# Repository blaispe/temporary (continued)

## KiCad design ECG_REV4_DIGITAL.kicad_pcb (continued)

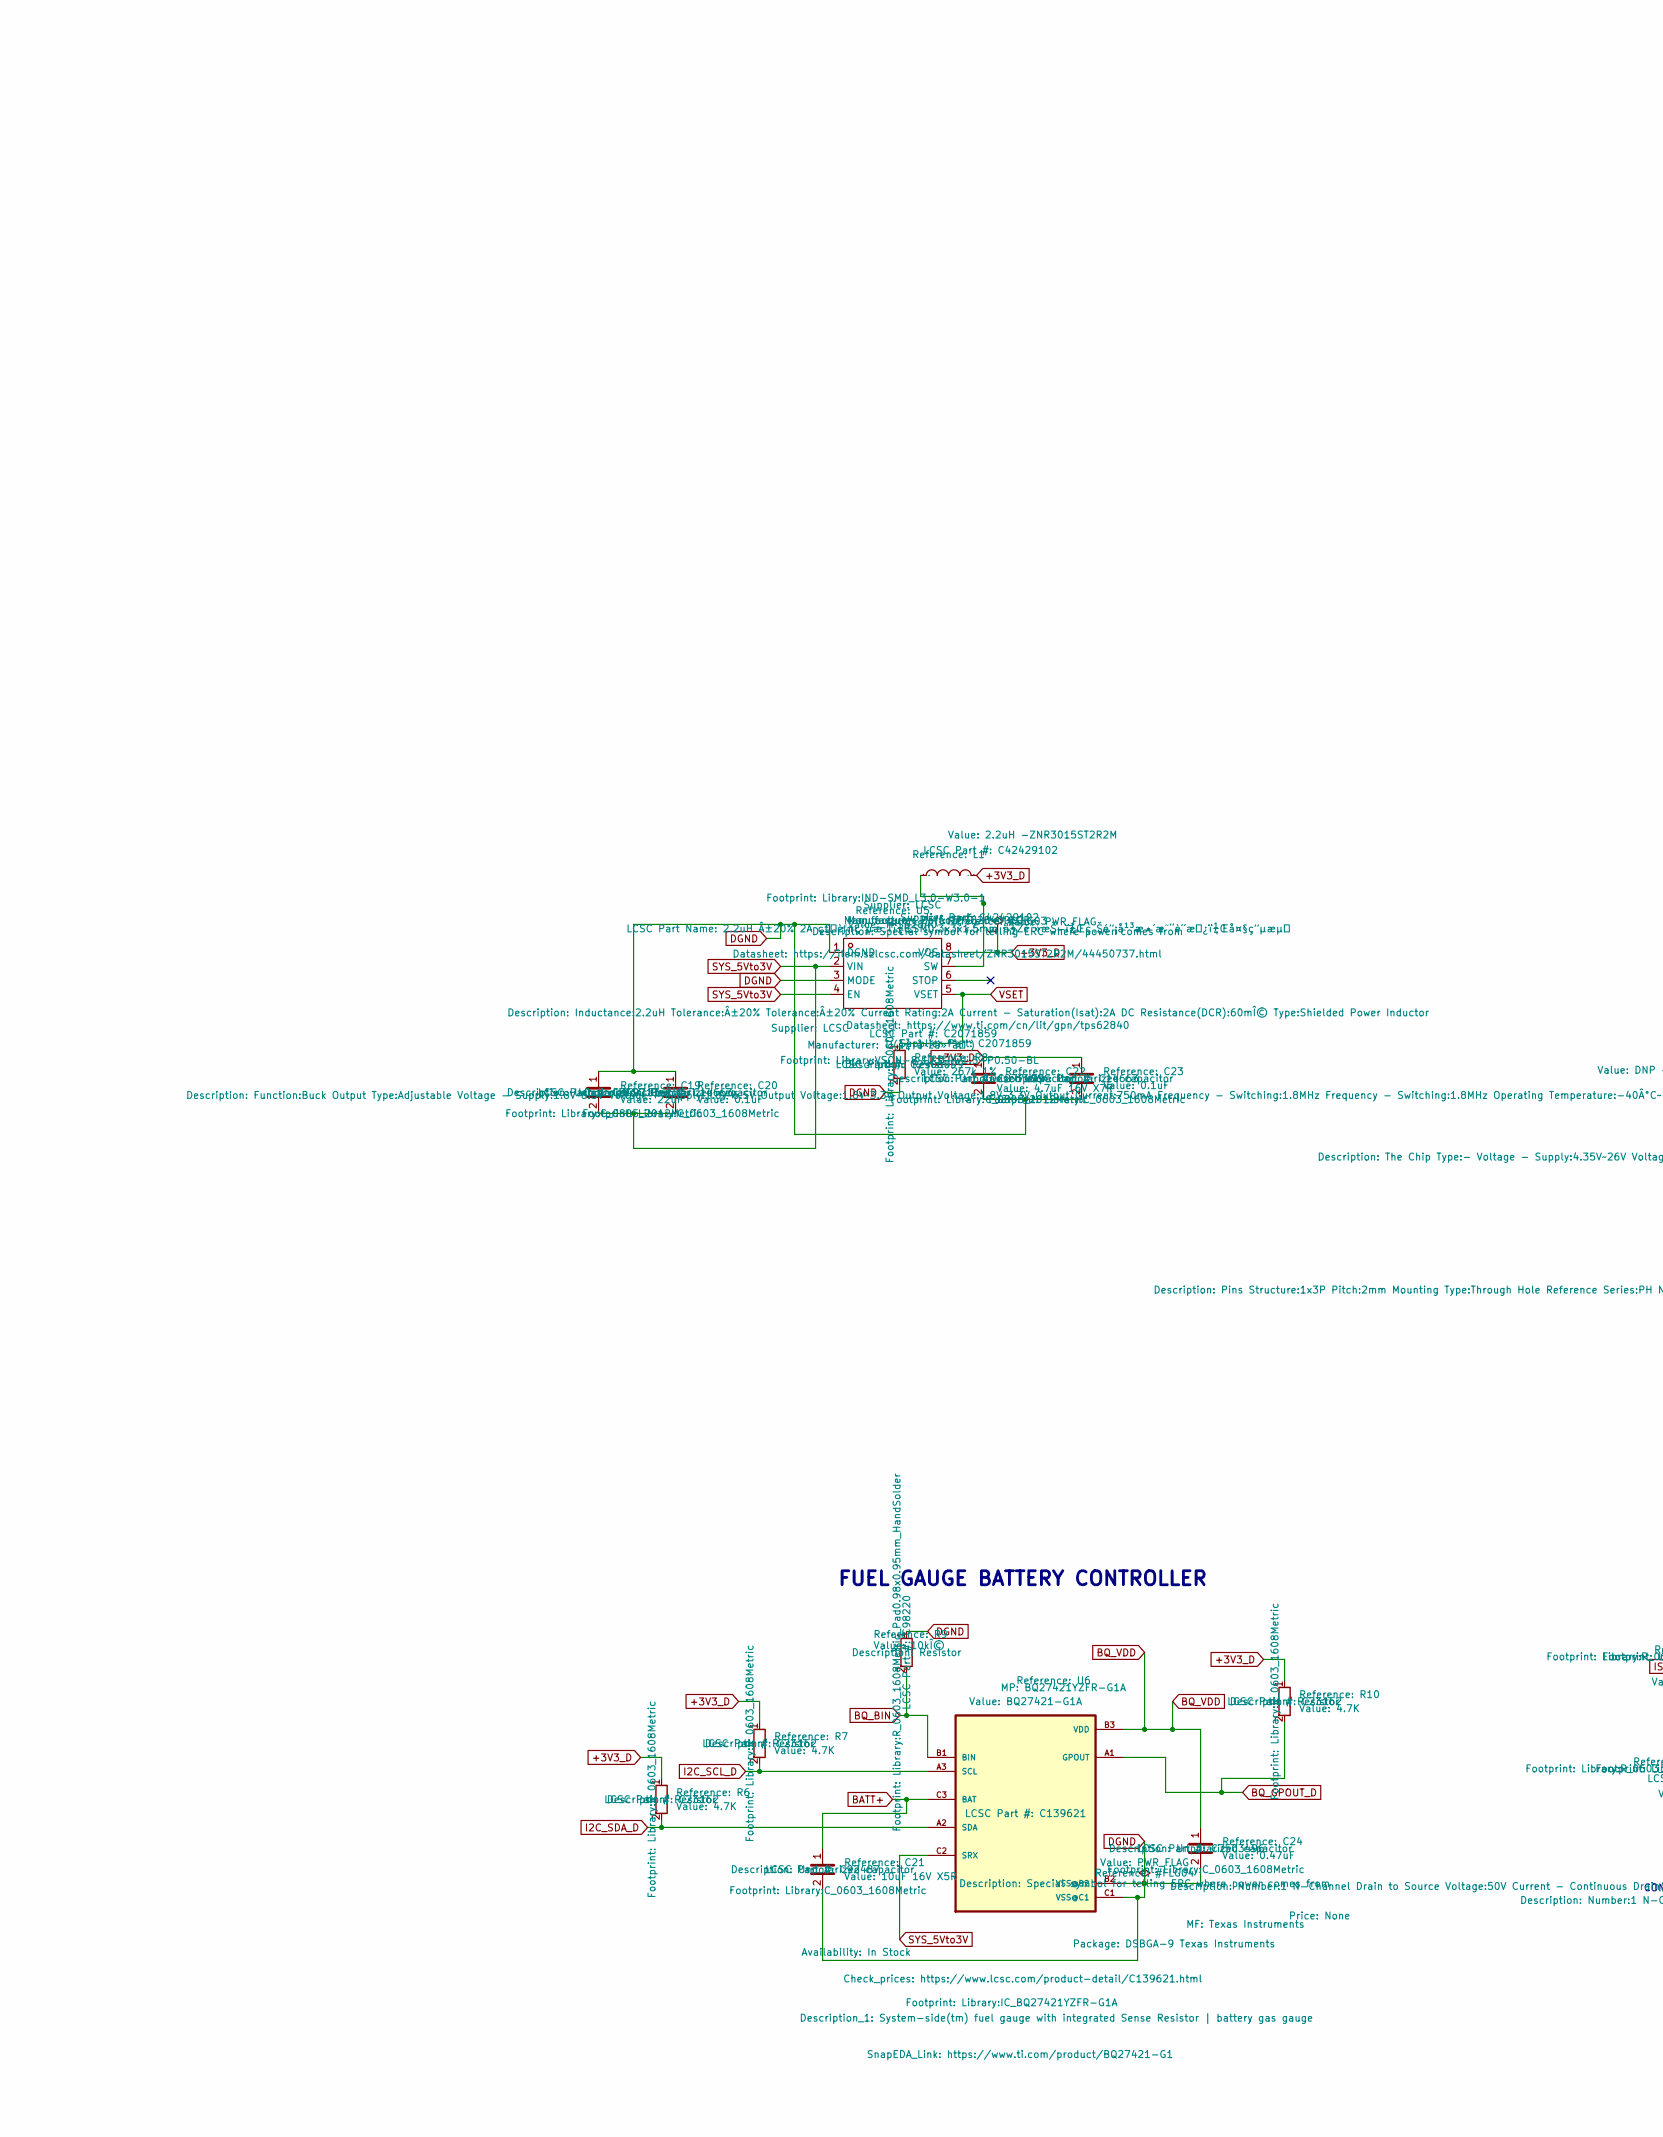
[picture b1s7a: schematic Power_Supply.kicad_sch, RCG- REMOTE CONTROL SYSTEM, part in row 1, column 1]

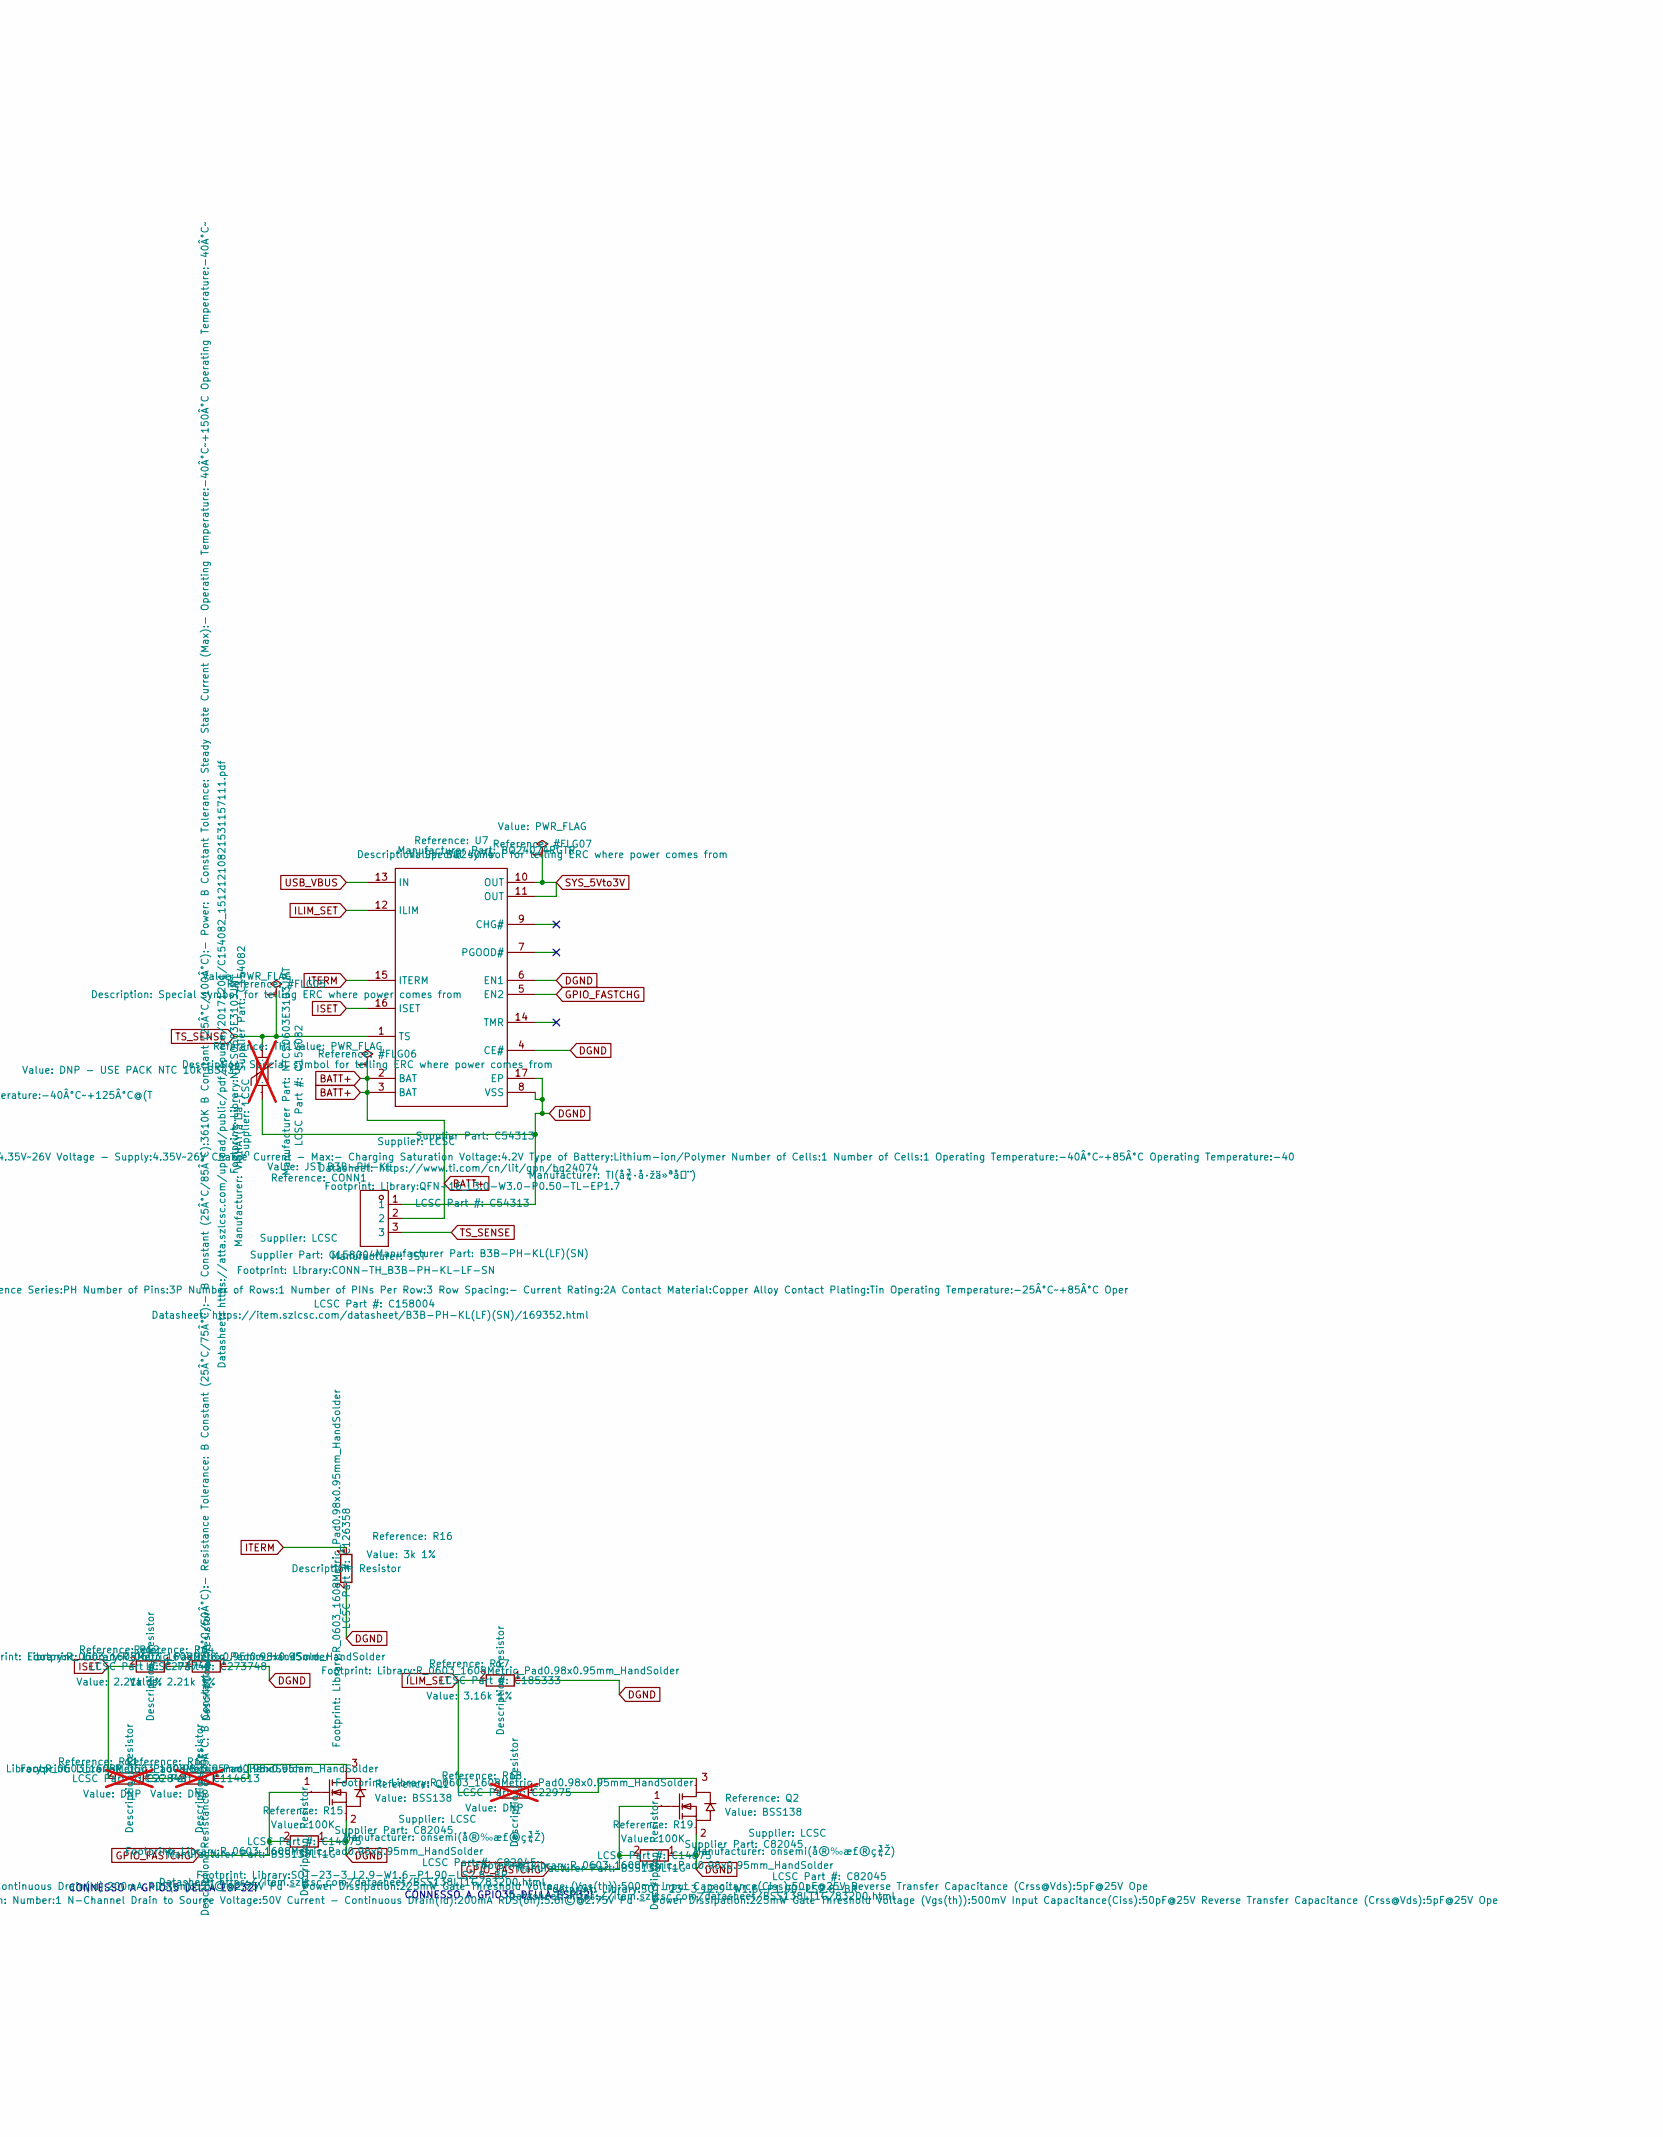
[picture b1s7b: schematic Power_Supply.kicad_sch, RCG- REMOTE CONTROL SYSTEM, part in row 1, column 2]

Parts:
C19: 22uF; C_0805_2012Metric; LCSC Part # C342717
C20, C23: 0.1uF; C_0603_1608Metric; LCSC Part # C14663
C21: 10uF 16V X5R; C_0603_1608Metric; LCSC Part # C92487
C22: 4.7uF 16V X7R; C_0805_2012Metric; LCSC Part # C277499
C24: 0.47uF; C_0603_1608Metric; LCSC Part # C7503496
CONN1: JST B3B-PH-KL; CONN-TH_B3B-PH-KL-LF-SN; Manufacturer Part B3B-PH-KL(LF)(SN); LCSC Part # C158004
L1: 2.2uH -ZNR3015ST2R2M; IND-SMD_L3.0-W3.0-1; LCSC Part # C42429102
Q1, Q2: BSS138; SOT-23-3_L2.9-W1.6-P1.90-LS2.8-BR; Manufacturer Part BSS138LT1G; LCSC Part # C82045
R6, R7, R10: 4.7K; R_0603_1608Metric; LCSC Part # C23162
R8: 267k 1%; R_0603_1608Metric; LCSC Part # C2906999
R9: 10kÎ©; R_0603_1608Metric_Pad0.98x0.95mm_HandSolder; LCSC Part # C98220
R11: DNP; R_0603_1608Metric_Pad0.98x0.95mm_HandSolder; LCSC Part # C22843; not fitted
R12, R14: 2.21k 1%; R_0603_1608Metric_Pad0.98x0.95mm_HandSolder; LCSC Part # C273748
R13: DNP; R_0603_1608Metric_Pad0.98x0.95mm_HandSolder; LCSC Part # C114613; not fitted
R15, R19: 100K; R_0603_1608Metric_Pad0.98x0.95mm_HandSolder; LCSC Part # C14675
R16: 3k 1%; R_0603_1608Metric_Pad0.98x0.95mm_HandSolder; LCSC Part # C126358
R17: 3.16k 1%; R_0603_1608Metric_Pad0.98x0.95mm_HandSolder; LCSC Part # C185333
R18: DNP; R_0603_1608Metric_Pad0.98x0.95mm_HandSolder; LCSC Part # C22975; not fitted
TH1: DNP - USE PACK NTC 10k B3435; NTCS0603E3103JMT; Manufacturer Part NTCS0603E3103JMT; LCSC Part # C154082; not fitted
U5: TPS62840; VSON-8_L2.0-W1.5-P0.50-BL; Manufacturer Part TPS62840DLCR; LCSC Part # C2071859
U6: BQ27421-G1A; IC_BQ27421YZFR-G1A; LCSC Part # C139621
U7: BQ24074; QFN-16_L3.0-W3.0-P0.50-TL-EP1.7; Manufacturer Part BQ24074RGTR; LCSC Part # C54313

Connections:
+3V3_D: C22.1, C23.1, L1.2, R6.1, R7.1, R10.1, U5.8 (VOS); also elsewhere on the board
BATT+: C21.1, CONN1.2, U6.C3 (BAT), U7.2 (BAT), U7.3 (BAT)
BQ_BIN: R9.2, U6.B1 (BIN)
BQ_GPOUT_D: R10.2, U6.A1 (GPOUT); also elsewhere on the board
BQ_VDD: C24.1, U6.B3 (VDD)
DGND: C19.1, C20.1, C21.2, C22.2, C23.2, C24.2, CONN1.1, Q1.2 (S), Q2.2 (S), R8.2, R9.1, R14.1, R15.1, R16.2, R17.1, R19.1, TH1.1, U5.1 (DGND), U5.3 (MODE), U6.B2 (VSS@B2), U6.C1 (VSS@C1), U7.4 (CE#), U7.6 (EN1), U7.8 (VSS), U7.17 (EP); also elsewhere on the board
GPIO_FASTCHG: Q1.1 (G), Q2.1 (G), R15.2, R19.2, U7.5 (EN2); also elsewhere on the board
I2C_SCL_D: R7.2, U6.A3 (SCL); also elsewhere on the board
I2C_SDA_D: R6.2, U6.A2 (SDA); also elsewhere on the board
ILIM_SET: R17.2, R18.2, U7.12 (ILIM)
ISET: R11.2, R12.2, U7.16 (ISET)
ITERM: R16.1, U7.15 (ITERM)
unnamed: Q1.3 (D), R13.1
unnamed: Q2.3 (D), R18.1
unnamed: R11.1, R13.2
unnamed: R12.1, R14.2
unnamed: L1.1, U5.7 (SW)
SYS_5Vto3V: C19.2, C20.2, U5.2 (VIN), U5.4 (EN), U6.C2 (SRX), U7.10 (OUT), U7.11 (OUT)
TS_SENSE: CONN1.3, TH1.2, U7.1 (TS)
USB_VBUS: U7.13 (IN); also elsewhere on the board
VSET: R8.1, U5.5 (VSET)

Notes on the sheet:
FUEL GAUGE BATTERY CONTROLLER
CONNESSO A GPIO35 DELLA ESP32!

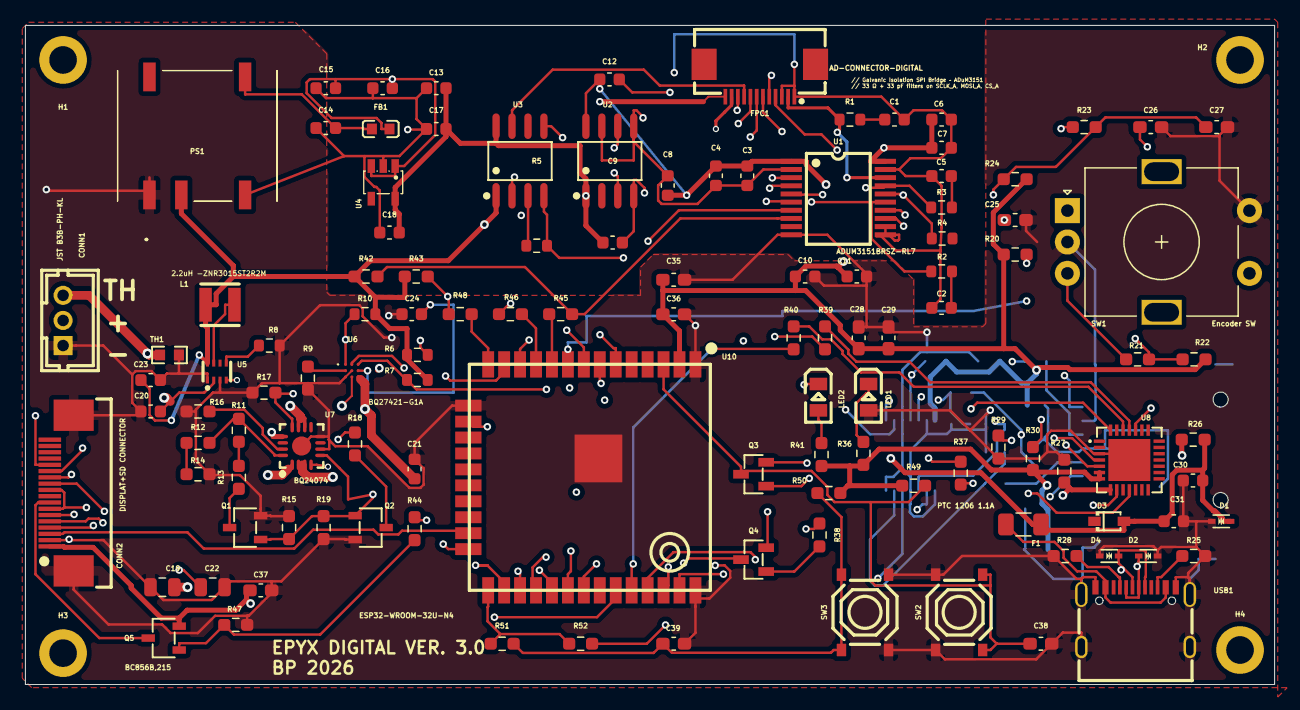
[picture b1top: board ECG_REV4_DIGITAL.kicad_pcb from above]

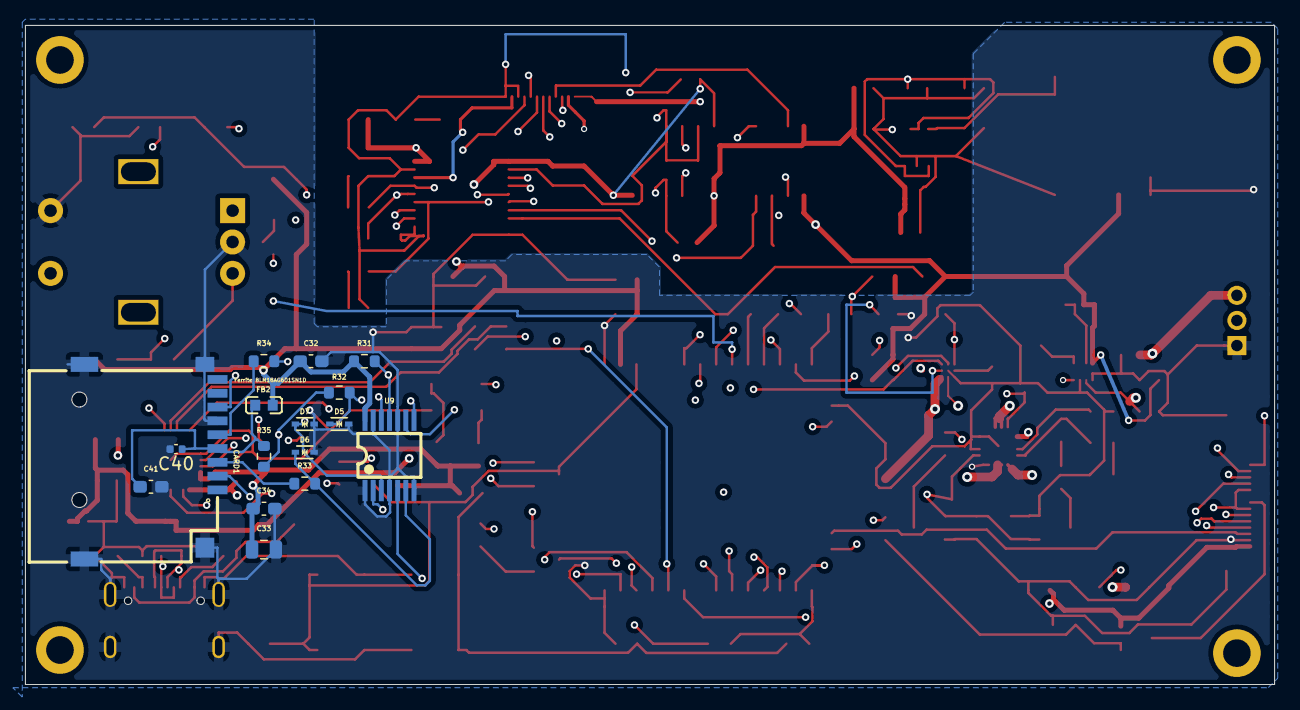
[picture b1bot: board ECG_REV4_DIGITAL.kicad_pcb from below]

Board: 4 copper layers, 99.5 x 52.5 mm, 135 parts (16 on the bottom side), 91 nets.

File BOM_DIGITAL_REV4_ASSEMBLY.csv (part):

"Reference","Value","Footprint","Quantity","DNP","Manufacturer","Manufacturer Part","MP","LCSC","Datasheet","Description"
"C1","33pF","Library:C_0603_1608Metric","1","","","","","C1663","","Unpolarized capacitor"
"C2","33pF","Library:C_0603_1608Metric","1","","","","","C1663","","Unpolarized capacitor"
"C3","0.1uF","Library:C_0603_1608Metric","1","","","","","C1591","","Unpolarized capacitor"
"C4","1uF","Library:C_0603_1608Metric","1","","","","","C29936","","Unpolarized capacitor"
"C5","33pF","Library:C_0603_1608Metric","1","","","","","C1663","","Unpolarized capacitor"
"C6","1uF","Library:C_0603_1608Metric","1","","","","","C29936","","Unpolarized capacitor"
"C7","0.1uF","Library:C_0603_1608Metric","1","","","","","C1591","","Unpolarized capacitor"
"C8","0.1uF","Library:C_0603_1608Metric","1","","","","","C1591","","Unpolarized capacitor"
"C9","0.1uF","Library:C_0603_1608Metric","1","","","","","C1591","","Unpolarized capacitor"
"C10","10uF","Library:C_0603_1608Metric","1","","","","","C380314","","Unpolarized capacitor"
"C11","0.1uF","Library:C_0603_1608Metric","1","","","","","C1591","","Unpolarized capacitor"
"C12","0.1uF","Library:C_0603_1608Metric","1","","","","","C1591","","Unpolarized capacitor"
"C13","0.1uF","Library:C_0603_1608Metric","1","","","","","C1591","","Unpolarized capacitor"
"C14","0.1uF","Library:C_0603_1608Metric","1","","","","","C1591","","Unpolarized capacitor"
"C15","10uF","Library:C_0603_1608Metric","1","","","","","C380314","","Unpolarized capacitor"
"C16","1uF","Library:C_0603_1608Metric","1","","","","","C29936","","Unpolarized capacitor"
"C17","1uF","Library:C_0603_1608Metric","1","","","","","C29936","","Unpolarized capacitor"
"C18","10uF","Library:C_0603_1608Metric","1","","","","","C380314","","Unpolarized capacitor"
"C19","22uF","Library:C_0805_2012Metric","1","","","","","C342717","","Unpolarized capacitor"
"C20","0.1uF","Library:C_0603_1608Metric","1","","","","","C14663","","Unpolarized capacitor"
"C21","10uF 16V X5R","Library:C_0603_1608Metric","1","","","","","C92487","","Unpolarized capacitor"
"C22","4.7uF 16V X7R","Library:C_0805_2012Metric","1","","","","","C277499","","Unpolarized capacitor"
"C23","0.1uF","Library:C_0603_1608Metric","1","","","","","C14663","","Unpolarized capacitor"
"C24","0.47uF","Library:C_0603_1608Metric","1","","","","","C7503496","","Unpolarized capacitor"
"C25","0.1uF","Library:C_0603_1608Metric_Pad1.08x0.95mm_HandSolder","1","","","","","C1591","","Unpolarized capacitor"
"C26","10nF","Library:C_0603_1608Metric_Pad1.08x0.95mm_HandSolder","1","","","","","C100042","","Unpolarized capacitor"
"C27","10nF","Library:C_0603_1608Metric_Pad1.08x0.95mm_HandSolder","1","","","","","C100042","","Unpolarized capacitor"
"C28","4.7uf","Library:C_0603_1608Metric_Pad1.08x0.95mm_HandSolder","1","","","","","C109456","","Unpolarized capacitor"
"C29","0.1uF","Library:C_0603_1608Metric_Pad1.08x0.95mm_HandSolder","1","","","","","C1591","","Unpolarized capacitor"
"C30","10uF","Library:C_0603_1608Metric","1","","","","","C380314","","Unpolarized capacitor"
"C31","0.1uF","Library:C_0603_1608Metric","1","","","","","C1591","",""
"C32","0.1uF","Library:C_0603_1608Metric_Pad1.08x0.95mm_HandSolder","1","","","","","C327087","","Unpolarized capacitor"
"C33","10uF","Library:C_0805_2012Metric","1","","","","","C6119906","","Unpolarized capacitor"
"C34","0.1uF","Library:C_0603_1608Metric_Pad1.08x0.95mm_HandSolder","1","","","","","C327087","","Unpolarized capacitor"
"C35","10uF 10V X5R","Library:C_0603_1608Metric_Pad1.08x0.95mm_HandSolder","1","","","CL10A106KP8NNNC","","C19702","",""
"C36","0.1uF","Library:C_0603_1608Metric_Pad1.08x0.95mm_HandSolder","1","","","","","C1591","","Unpolarized capacitor"
"C37","0.1uF","Library:C_0603_1608Metric_Pad1.08x0.95mm_HandSolder","1","","","","","C14663","","Unpolarized capacitor"
"C38","0.1uF","Library:C_0603_1608Metric_Pad1.08x0.95mm_HandSolder","1","","","","","C1591","","Unpolarized capacitor"
"C39","0.1uF","Library:C_0603_1608Metric_Pad1.08x0.95mm_HandSolder","1","","","","","C1591","","Unpolarized capacitor"
"C40","100nF 16V X7R","Library:C_0402_1005Metric","1","","","","","C60474","","Unpolarized capacitor"
"C41","10uF 10V X7R","Library:C_0603_1608Metric_Pad1.08x0.95mm_HandSolder","1","","","","","C22399627","","Unpolarized capacitor"
"CARD1","SD-CARD","Library:TF-SMD_TF-PUSH","1","","SHOU HAN(é¦–éŸ©)","TF PUSH","","C393941","https://item.szlcsc.com/datasheet/TF%2520PUSH/372553.html","Card Connection Mode:Push-Push Card Type:MicroSD Card (TF Card) Connector Type:Connector and Ejector Additional Card Detection Pins:No Supplementary Features:- Height Above Board:2mm Operating Temperature:-25Â°C~+90Â°C Operating Temperature:-25Â°C~+90Â°C"
"CONN1","JST B3B-PH-KL","Library:CONN-TH_B3B-PH-KL-LF-SN","1","","JST","B3B-PH-KL(LF)(SN)","","C158004","https://item.szlcsc.com/datasheet/B3B-PH-KL(LF)(SN)/169352.html","Pins Structure:1x3P Pitch:2mm Mounting Type:Through Hole Reference Series:PH Number of Pins:3P Number of Rows:1 Number of PINs Per Row:3 Row Spacing:- Current Rating:2A Contact Material:Copper Alloy Contact Plating:Tin Operating Temperature:-25Â°C~+85Â°C Oper"
"CONN2","DISPLAT+SD CONNECTOR","Library:FPC-SMD_18P-P0.50_HC-FPC-0.5-18P-CXH20","1","","XYECONN(è¾›è¯‘)","FPC02-S0.5-18AH2.0","","C19267915","https://item.szlcsc.com/datasheet/FPC02-S0.5-18AH2.0/20525231.html","Locking Feature:Slide Lock Contact Type:Top Contact Number of Contacts:18P Pitch:0.5mm Mounting Type:Surface Mount, Right Angle Height Above Board:2mm"
"D1","LESD5D5.0CT1G","Library:SOD-523_L1.2-W0.8-LS1.6-BI","1","","LRC(ä¹å±±æ— çº¿ç”µ)","LESD5D5.0CT1G","","C5199850","https://lcsc.com/eda_search?q=C383211&%26type=1&ref=editor",""
"D2","LESD5D5.0CT1G","Library:SOD-523_L1.2-W0.8-LS1.6-BI","1","","LRC(ä¹å±±æ— çº¿ç”µ)","LESD5D5.0CT1G","","C5199850","https://lcsc.com/eda_search?q=C383211&%26type=1&ref=editor",""
"D4","LESD5D5.0CT1G","Library:SOD-523_L1.2-W0.8-LS1.6-BI","1","","LRC(ä¹å±±æ— çº¿ç”µ)","LESD5D5.0CT1G","","C5199850","https://lcsc.com/eda_search?q=C383211&%26type=1&ref=editor",""
"D5","LESD5D5.0CT1G","Library:SOD-523_L1.2-W0.8-LS1.6-BI","1","","LRC(ä¹å±±æ— çº¿ç”µ)","LESD5D5.0CT1G","","C5199850","https://lcsc.com/eda_search?q=C383211&%26type=1&ref=editor",""
"D6","LESD5D5.0CT1G","Library:SOD-523_L1.2-W0.8-LS1.6-BI","1","","LRC(ä¹å±±æ— çº¿ç”µ)","LESD5D5.0CT1G","","C5199850","https://lcsc.com/eda_search?q=C383211&%26type=1&ref=editor",""
"D7","LESD5D5.0CT1G","Library:SOD-523_L1.2-W0.8-LS1.6-BI","1","","LRC(ä¹å±±æ— çº¿ç”µ)","LESD5D5.0CT1G","","C5199850","https://lcsc.com/eda_search?q=C383211&%26type=1&ref=editor",""
"F1","PTC 1206 1.1A","Library:Fuse_1206_3216Metric","1","","","","","C2803344","","Fuse"
"FB1","Ferrite BLM18AG601SN1D","Library:L0603","1","","muRata(æ‘ç”°)","BLM18AG601SN1D","","C19330","https://item.szlcsc.com/datasheet/BLM18EG601SN1D/21056.html","Impedance @ Frequency:600Î©@100MHz Tolerance:Â±25% Tolerance:Â±25% DC Resistance(DCR):350mÎ© Current Rating:500mA Number of Circuits:1 Operating Temperature:-55Â°C~+125Â°C Operating Temperature:-55Â°C~+125Â°C"
"FB2","Ferrite BLM18AG601SN1D","Library:L0603","1","","muRata(æ‘ç”°)","BLM18AG601SN1D","","C19330","https://item.szlcsc.com/datasheet/BLM18EG601SN1D/21056.html","Impedance @ Frequency:600Î©@100MHz Tolerance:Â±25% Tolerance:Â±25% DC Resistance(DCR):350mÎ© Current Rating:500mA Number of Circuits:1 Operating Temperature:-55Â°C~+125Â°C Operating Temperature:-55Â°C~+125Â°C"
"FPC1","AD-CONNECTOR-DIGITAL","Library:FPC-SMD_12P-P0.50_XUNPU_FPC-05F-12PH20","1","","XUNPU(讯普)","FPC-05F-12PH20","","C2856799","https://atta.szlcsc.com/upload/public/pdf/source/20210922/C2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","Locking Feature:Hinged Lid Contact Type:Surface Mount Number of Contacts:12P Pitch:0.5mm Mounting Type:Bottom Contact FFC, FCB Thickness:0.3mm FFC, FCB Thickness:0.3mm Height Above Board:2mm Contact Material:Phosphor Bronze Contact Plating:Tin Operating T"
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
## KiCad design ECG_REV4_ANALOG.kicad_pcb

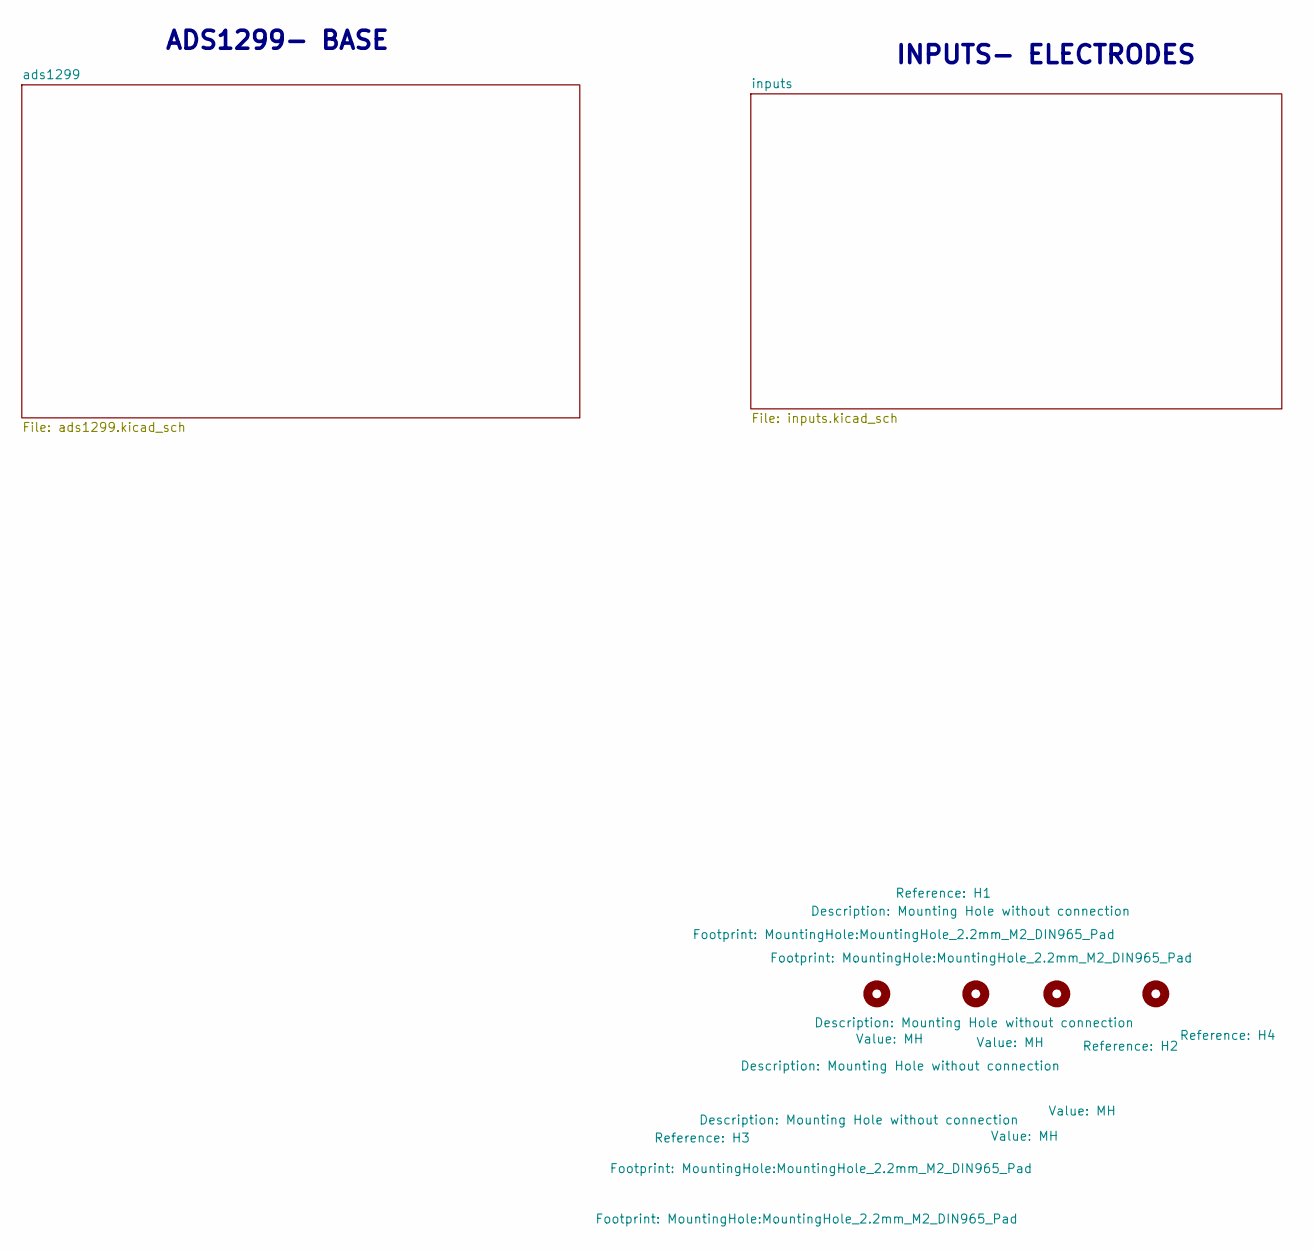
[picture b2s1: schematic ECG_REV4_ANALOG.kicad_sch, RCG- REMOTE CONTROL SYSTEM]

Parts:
H1, H2, H3, H4: MH; MountingHole_2.2mm_M2_DIN965_Pad

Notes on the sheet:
INPUTS- ELECTRODES
ADS1299- BASE

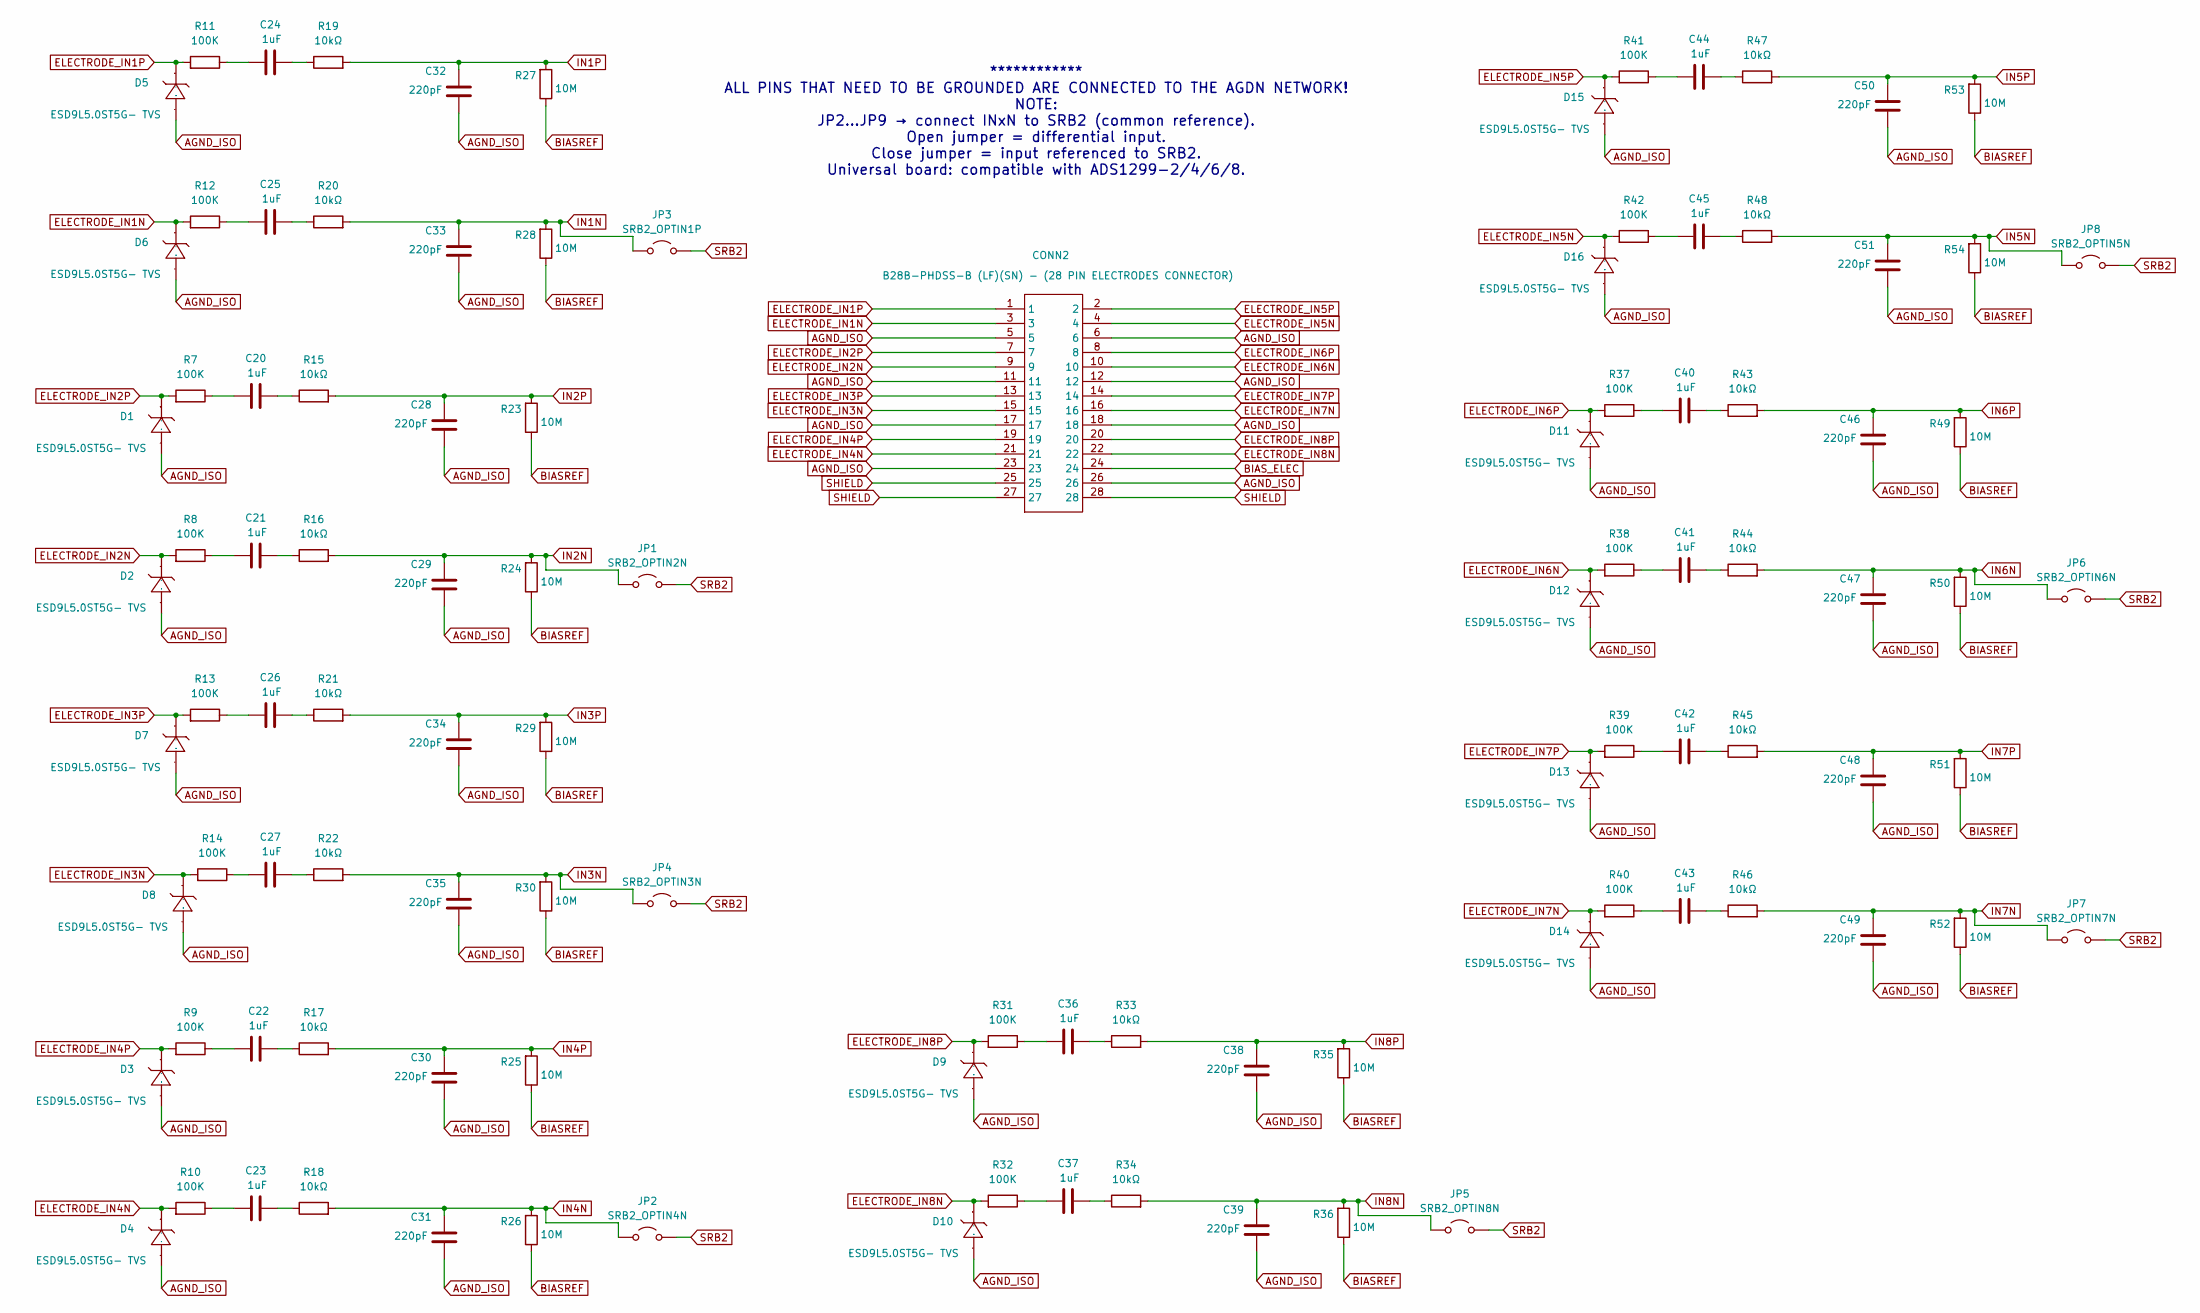
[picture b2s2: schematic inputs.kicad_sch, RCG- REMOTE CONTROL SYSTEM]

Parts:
C20, C21, C22, C23, C24, C25, C26, C27, C36, C37, C40, C41, C42, C43, C44, C45: 1uF; C_0603_1608Metric_Pad1.08x0.95mm_HandSolder; LCSC Part # C15849
C28, C29, C30, C31, C32, C33, C34, C35, C38, C39, C46, C47, C48, C49, C50, C51: 220pF; C_0603_1608Metric_Pad1.08x0.95mm_HandSolder; LCSC Part # C1603
CONN2: B28B-PHDSS-B (LF)(SN) - (28 PIN ELECTRODES CONNEC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; CONN-TH-28P-P2.00_B28B-PHDSS-B-LF-SN; Manufacturer Part B28B-PHDSS-B(LF)(SN); LCSC Part # C160329
D1, D2, D3, D4, D5, D6, D7, D8, D9, D10, D11, D12, D13, D14, D15, D16: ESD9L5.0ST5G- TVS; ESD9L5.0ST5G; Manufacturer Part ESD9L5.0ST5G; LCSC Part # C41399458
JP1: SRB2_OPTIN2N; SolderJumper-2_P1.3mm_Open_Pad1.0x1.5mm
JP2: SRB2_OPTIN4N; SolderJumper-2_P1.3mm_Open_Pad1.0x1.5mm
JP3: SRB2_OPTIN1P; SolderJumper-2_P1.3mm_Open_Pad1.0x1.5mm
JP4: SRB2_OPTIN3N; SolderJumper-2_P1.3mm_Open_Pad1.0x1.5mm
JP5: SRB2_OPTIN8N; SolderJumper-2_P1.3mm_Open_Pad1.0x1.5mm
JP6: SRB2_OPTIN6N; SolderJumper-2_P1.3mm_Open_Pad1.0x1.5mm
JP7: SRB2_OPTIN7N; SolderJumper-2_P1.3mm_Open_Pad1.0x1.5mm
JP8: SRB2_OPTIN5N; SolderJumper-2_P1.3mm_Open_Pad1.0x1.5mm
R7, R8, R9, R10, R11, R12, R13, R14, R31, R32, R37, R38, R39, R40, R41, R42: 100K; R_0603_1608Metric_Pad0.98x0.95mm_HandSolder; LCSC Part # C14675
R15, R16, R17, R18, R19, R20, R21, R22, R33, R34, R43, R44, R45, R46, R47, R48: 10kΩ; R_0603_1608Metric_Pad0.98x0.95mm_HandSolder; LCSC Part # C98220
R23, R24, R25, R26, R27, R28, R29, R30, R35, R36, R49, R50, R51, R52, R53, R54: 10M; R_0603_1608Metric_Pad0.98x0.95mm_HandSolder; LCSC Part # C26097

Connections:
AGND_ISO: C28.1, C29.1, C30.1, C31.1, C32.1, C33.1, C34.1, C35.1, C38.1, C39.1, C46.1, C47.1, C48.1, C49.1, C50.1, C51.1, CONN2.5, CONN2.6, CONN2.11, CONN2.12, CONN2.17, CONN2.18, CONN2.23, CONN2.26, D1.2 (A), D2.2 (A), D3.2 (A), D4.2 (A), D5.2 (A), D6.2 (A), D7.2 (A), D8.2 (A), D9.2 (A), D10.2 (A), D11.2 (A), D12.2 (A), D13.2 (A), D14.2 (A), D15.2 (A), D16.2 (A); also elsewhere on the board
BIASREF: R23.1, R24.1, R25.1, R26.1, R27.1, R28.1, R29.1, R30.1, R35.1, R36.1, R49.1, R50.1, R51.1, R52.1, R53.1, R54.1; also elsewhere on the board
BIAS_ELEC: CONN2.24; also elsewhere on the board
ELECTRODE_IN1N: CONN2.3, D6.1 (C), R12.2
ELECTRODE_IN1P: CONN2.1, D5.1 (C), R11.2
ELECTRODE_IN2N: CONN2.9, D2.1 (C), R8.2
ELECTRODE_IN2P: CONN2.7, D1.1 (C), R7.2
ELECTRODE_IN3N: CONN2.15, D8.1 (C), R14.2
ELECTRODE_IN3P: CONN2.13, D7.1 (C), R13.2
ELECTRODE_IN4N: CONN2.21, D4.1 (C), R10.2
ELECTRODE_IN4P: CONN2.19, D3.1 (C), R9.2
ELECTRODE_IN5N: CONN2.4, D16.1 (C), R42.2
ELECTRODE_IN5P: CONN2.2, D15.1 (C), R41.2
ELECTRODE_IN6N: CONN2.10, D12.1 (C), R38.2
ELECTRODE_IN6P: CONN2.8, D11.1 (C), R37.2
ELECTRODE_IN7N: CONN2.16, D14.1 (C), R40.2
ELECTRODE_IN7P: CONN2.14, D13.1 (C), R39.2
ELECTRODE_IN8N: CONN2.22, D10.1 (C), R32.2
ELECTRODE_IN8P: CONN2.20, D9.1 (C), R31.2
IN1N: C33.2, JP3.1 (A), R20.2, R28.2; also elsewhere on the board
IN1P: C32.2, R19.2, R27.2; also elsewhere on the board
IN2N: C29.2, JP1.1 (A), R16.2, R24.2; also elsewhere on the board
IN2P: C28.2, R15.2, R23.2; also elsewhere on the board
IN3N: C35.2, JP4.1 (A), R22.2, R30.2; also elsewhere on the board
IN3P: C34.2, R21.2, R29.2; also elsewhere on the board
IN4N: C31.2, JP2.1 (A), R18.2, R26.2; also elsewhere on the board
IN4P: C30.2, R17.2, R25.2; also elsewhere on the board
IN5N: C51.2, JP8.1 (A), R48.2, R54.2; also elsewhere on the board
IN5P: C50.2, R47.2, R53.2; also elsewhere on the board
IN6N: C47.2, JP6.1 (A), R44.2, R50.2; also elsewhere on the board
IN6P: C46.2, R43.2, R49.2; also elsewhere on the board
IN7N: C49.2, JP7.1 (A), R46.2, R52.2; also elsewhere on the board
IN7P: C48.2, R45.2, R51.2; also elsewhere on the board
IN8N: C39.2, JP5.1 (A), R34.2, R36.2; also elsewhere on the board
IN8P: C38.2, R33.2, R35.2; also elsewhere on the board
unnamed: C20.1, R15.1
unnamed: C20.2, R7.1
unnamed: C21.1, R16.1
unnamed: C21.2, R8.1
unnamed: C22.1, R9.1
unnamed: C22.2, R17.1
unnamed: C23.1, R18.1
unnamed: C23.2, R10.1
unnamed: C24.1, R19.1
unnamed: C24.2, R11.1
unnamed: C25.1, R20.1
unnamed: C25.2, R12.1
unnamed: C26.1, R21.1
unnamed: C26.2, R13.1
unnamed: C27.1, R22.1
unnamed: C27.2, R14.1
unnamed: C36.1, R33.1
unnamed: C36.2, R31.1
unnamed: C37.1, R34.1
unnamed: C37.2, R32.1
unnamed: C40.1, R43.1
unnamed: C40.2, R37.1
unnamed: C41.1, R44.1
unnamed: C41.2, R38.1
unnamed: C42.1, R45.1
unnamed: C42.2, R39.1
unnamed: C43.1, R46.1
unnamed: C43.2, R40.1
unnamed: C44.1, R47.1
unnamed: C44.2, R41.1
unnamed: C45.1, R48.1
unnamed: C45.2, R42.1
SHIELD: CONN2.25, CONN2.27, CONN2.28
SRB2: JP1.2 (B), JP2.2 (B), JP3.2 (B), JP4.2 (B), JP5.2 (B), JP6.2 (B), JP7.2 (B), JP8.2 (B); also elsewhere on the board

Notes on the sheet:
************ ALL PINS THAT NEED TO BE GROUNDED ARE CONNECTED TO THE AGDN NETWORK! NOTE: JP2…JP9 → connect INxN to SRB2 (common reference). Open jumper = differential input. Close jumper = input referenced to SRB2. Universal board: compatible with ADS1299-2/4/6/8.
